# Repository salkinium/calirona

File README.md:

# Calirona: A calibration robot for Corona

The [Corona][corona] headphones use a HMC6343 compass for heading information which needs to be calibrated from time to time.
To do this, a robot rotates the headphones around two axis while the compass is in calibration mode.

The main design goals of this project are to:

-	calibrate the compass,
-	minimize the required technical knowledge to operate the robot,
-	test the compass functionality to catch the most obvious malfunctions.

This project was designed and manufactured at [The Media Computing Group][i10].

## Design

The robot can move the headphones around both two axes a full 360°, which are supported using ball bearings. The z-axis uses a dish which holds the headphones.

Since the power and signal lines for the headphones and second axis motor need to be relayed through both axis, the robot cannot rotate infinitely around its axis.  
Therefore two position switches exist, which allow the robot to rotate its axes into known safe positions before attempting a rotation.  
The robot will then rotate 360° around the x-axis, then 360° around the z-axis, and then reverse all rotations until it has reached the starting state again.

The robot is controlled by two buttons Start and Stop, and can display its internal state through leds for power, busy, headphone error and mechanical error.  
The mapping is as follows:

- START: initialize and start the calibration.
- STOP: stop robot movement (short press), release motors and reset robot (long press)
- Busy (blue): blinks, when an operation is in progress, otherwise off
- Headphone (orange): blinks, when no headphone is connected, or it is unresponsive (perhaps broken), otherwise on
- Mechanical Error (red): blinks, when the robot detected an invalid mechanical state (broken or blocked motor), otherwise off

## Usage

The basic usage of the robots is as follows:

1. Plug in the power cord. The green power led should light up and the headphone error led should blink.
2. Place the headphone into the holder drum and plug in the headphone jack. The headphone error led should stop blinking and turn on fully, unless the headphone is broken.
3. Press START. The robot will initialize its axes.
4. Press START again. The robot will do two rotations while calibrating the headphones.
5. Once the robot stopped moving, unplug the now calibrated headphones and remove them.

If the robot detected an invalid state during any of the actions, it will stop moving and blink an error led.

**Press the STOP button anytime to stop the robot from moving!**  
Pressing the STOP button for a longer time resets the robot.

## Organization

This repository is organized as follows:

- 	The *hardware* folder contains all hardware files for the robot.
	-	*hardware/et* contains the PCB schematics and layouts.
	-	*hardware/mech* contains the vector files of all mechanical parts of the robot (for the lasercutter).
- 	The *software* folder contains the software for the robot.
	- 	*software/source* contains the actual application code for this robot.
	-	*software/xpcc* contains the git submodule for the xpcc.io microcontroller framework.

All hardware and embedded software was designed by [Niklas Hauser][hauser].

[i10]: http://hci.rwth-aachen.de
[corona]: http://hci.rwth-aachen.de/corona
[hauser]: http://hci.rwth-aachen.de/hauser

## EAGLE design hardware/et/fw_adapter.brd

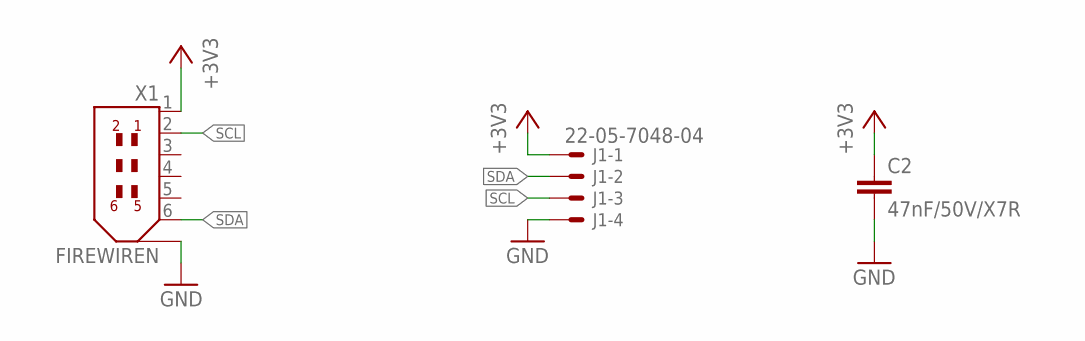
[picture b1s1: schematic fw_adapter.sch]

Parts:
C2: 47nF/50V/X7R; C0603K
J1: 22-05-7048-04; 7395-04
X1: FIREWIREN; IEEE1394_90DEG_PINS_NORMAL

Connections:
+3V3: C2.1, J1.1, X1.1
GND: C2.2, J1.4, X1.M1 (7), X1.M2 (7)
SCL: J1.3, X1.2
SDA: J1.2, X1.6

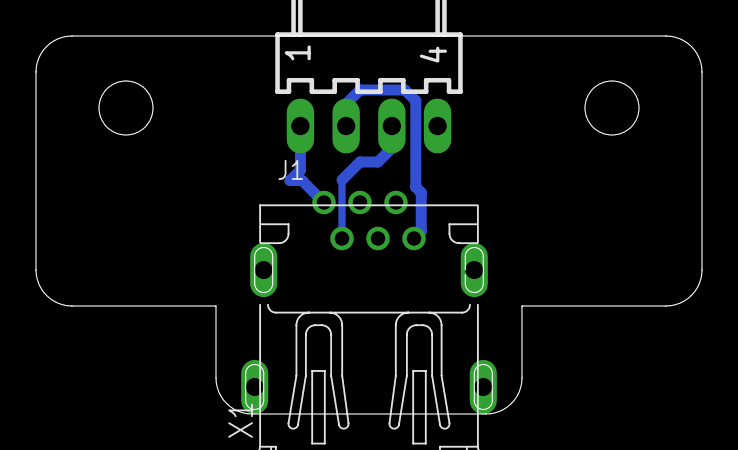
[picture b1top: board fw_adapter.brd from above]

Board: 2 copper layers, 37.0 x 21.0 mm, 3 parts (1 on the bottom side), 4 nets.

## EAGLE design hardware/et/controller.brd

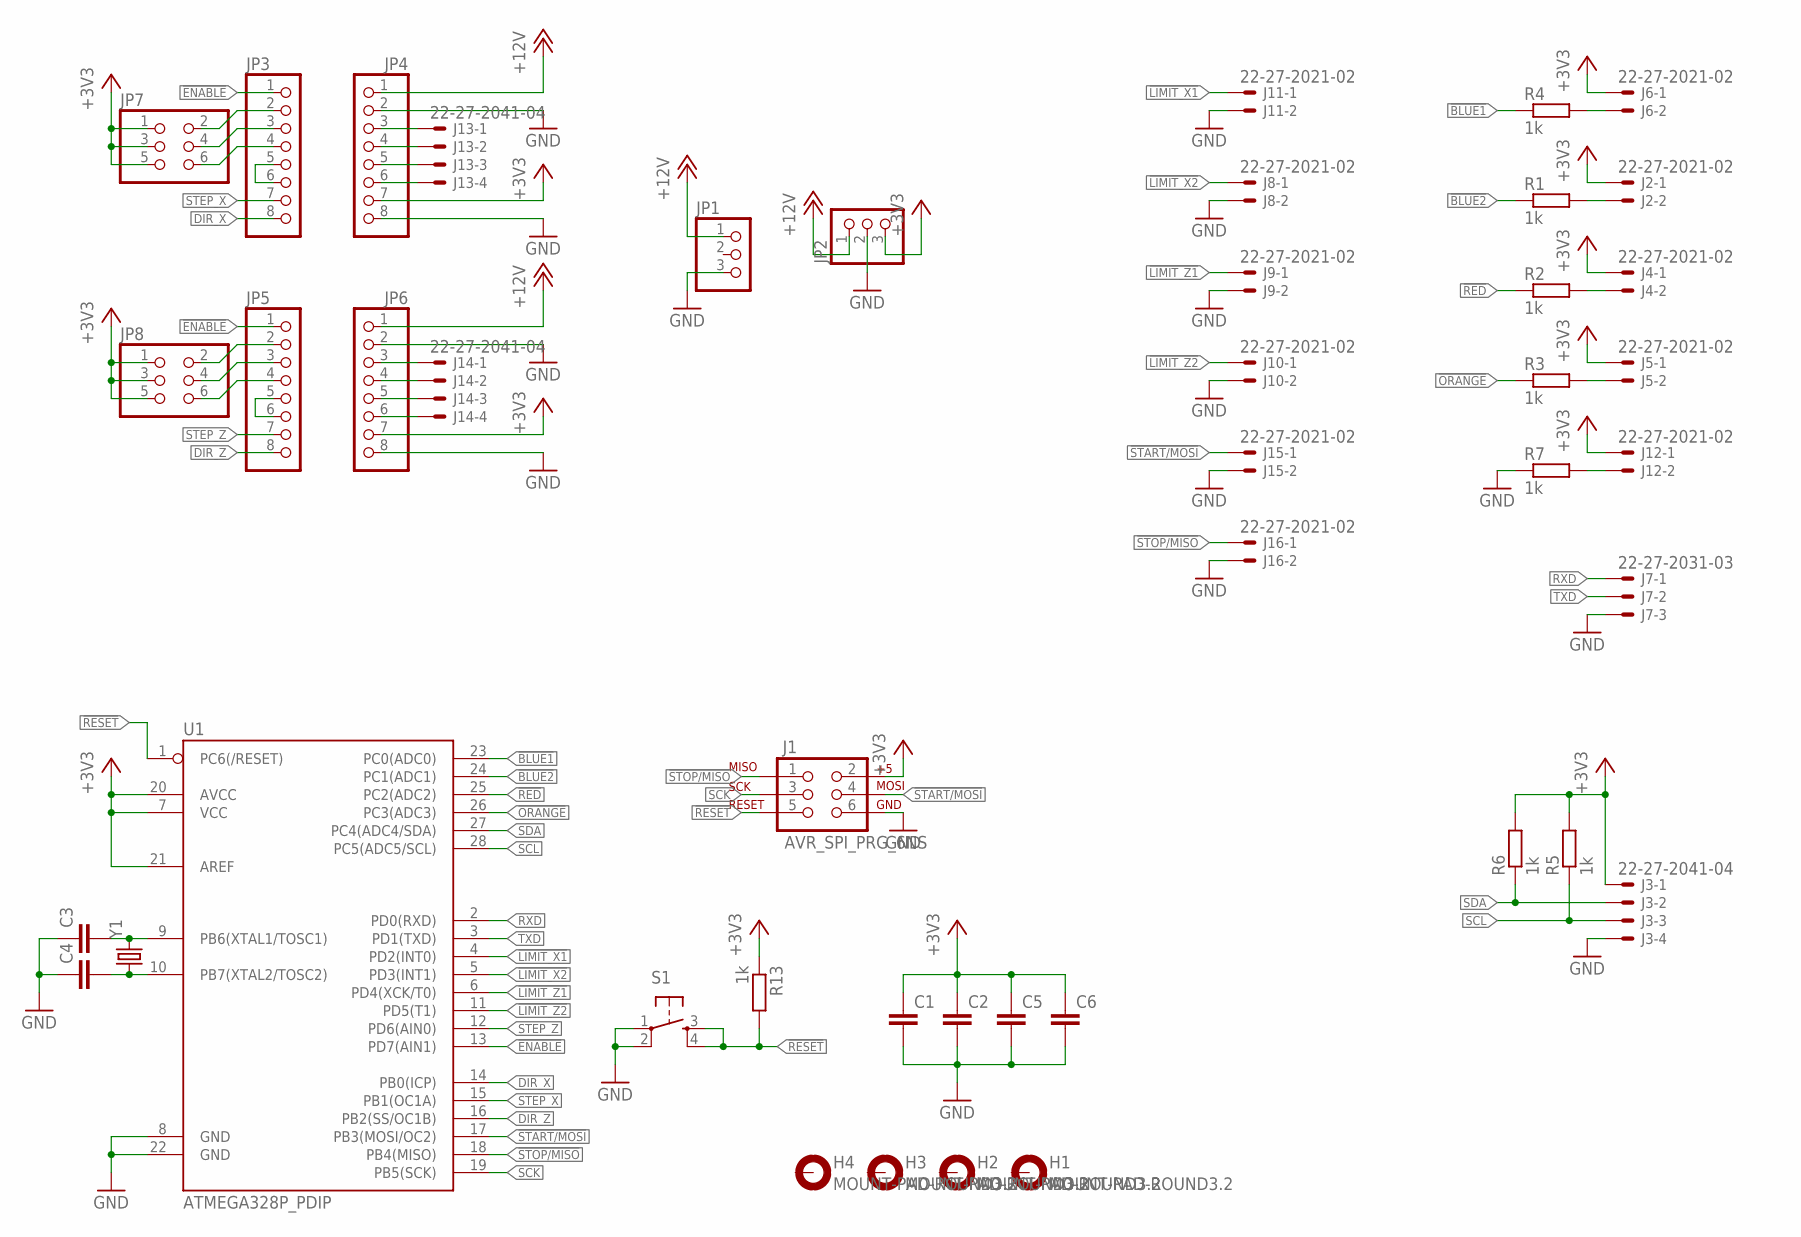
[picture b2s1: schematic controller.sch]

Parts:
C1, C2, C5, C6: C-EUC0603; C0603
C3, C4: C-EUC0603K; C0603K
H1, H2, H3, H4: MOUNT-PAD-ROUND3.2; 3,2-PAD
J1: AVR_SPI_PRG_6NS; 2X3-NS
J2, J4, J5, J6, J8, J9, J10, J11, J12, J15, J16: 22-27-2021-02; 6410-02
J3, J13, J14: 22-27-2041-04; 6410-04
J7: 22-27-2031-03; 6410-03
JP1, JP2: PINHD-1X3; 1X03
JP3, JP4, JP5, JP6: PINHD-1X8; 1X08
JP7, JP8: PINHD-2X3; 2X03
R1, R2, R3, R4, R5, R6, R7, R13: 1k; R0603
S1: TAC_SWITCHPTH; TACTILE-PTH
U1: ATMEGA328P_PDIP; DIL28-3
Y1: CRYSTALHC49UV; HC49U-V

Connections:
!BLUE1: R4.1, U1.23 (PC0(ADC0))
!BLUE2: R1.1, U1.24 (PC1(ADC1))
!ENABLE: JP3.1, JP5.1, U1.13 (PD7(AIN1))
!LIMIT_X1: J11.1, U1.4 (PD2(INT0))
!LIMIT_X2: J8.1, U1.5 (PD3(INT1))
!LIMIT_Z1: J9.1, U1.6 (PD4(XCK/T0))
!LIMIT_Z2: J10.1, U1.11 (PD5(T1))
!ORANGE: R3.1, U1.26 (PC3(ADC3))
!RED: R2.1, U1.25 (PC2(ADC2))
!RESET: J1.5, R13.2, S1.3, S1.4, U1.1 (PC6(/RESET))
!START/MOSI: J1.4, J15.1, U1.17 (PB3(MOSI/OC2))
!STOP/MISO: J1.1, J16.1, U1.18 (PB4(MISO))
+3V3: C1.1, C2.1, C5.1, C6.1, J1.2, J2.1, J3.1, J4.1, J5.1, J6.1, J12.1, JP2.3, JP4.7, JP6.7, JP7.1, JP7.3, JP7.5, JP8.1, JP8.3, JP8.5, R5.2, R6.2, R13.1, U1.7 (VCC), U1.20 (AVCC), U1.21 (AREF)
+12V: JP1.1, JP2.1, JP4.1, JP6.1
DIR_X: JP3.8, U1.14 (PB0(ICP))
DIR_Z: JP5.8, U1.16 (PB2(SS/OC1B))
GND: C1.2, C2.2, C3.1, C4.1, C5.2, C6.2, J1.6, J3.4, J7.3, J8.2, J9.2, J10.2, J11.2, J15.2, J16.2, JP1.3, JP2.2, JP4.2, JP4.8, JP6.2, JP6.8, R7.1, S1.1, S1.2, U1.8 (GND), U1.22 (GND)
unnamed: C3.2, U1.9 (PB6(XTAL1/TOSC1)), Y1.2
unnamed: C4.2, U1.10 (PB7(XTAL2/TOSC2)), Y1.1
unnamed: J4.2, R2.2
unnamed: J2.2, R1.2
unnamed: J5.2, R3.2
unnamed: J6.2, R4.2
unnamed: JP3.5, JP3.6
unnamed: JP3.4, JP7.6
unnamed: JP3.3, JP7.4
unnamed: JP3.2, JP7.2
unnamed: J12.2, R7.2
unnamed: JP5.5, JP5.6
unnamed: JP5.4, JP8.6
unnamed: JP5.3, JP8.4
unnamed: JP5.2, JP8.2
unnamed: J13.1, JP4.3
unnamed: J13.2, JP4.4
unnamed: J13.3, JP4.5
unnamed: J13.4, JP4.6
unnamed: J14.1, JP6.3
unnamed: J14.2, JP6.4
unnamed: J14.3, JP6.5
unnamed: J14.4, JP6.6
RXD: J7.1, U1.2 (PD0(RXD))
SCK: J1.3, U1.19 (PB5(SCK))
SCL: J3.3, R5.1, U1.28 (PC5(ADC5/SCL))
SDA: J3.2, R6.1, U1.27 (PC4(ADC4/SDA))
STEP_X: JP3.7, U1.15 (PB1(OC1A))
STEP_Z: JP5.7, U1.12 (PD6(AIN0))
TXD: J7.2, U1.3 (PD1(TXD))

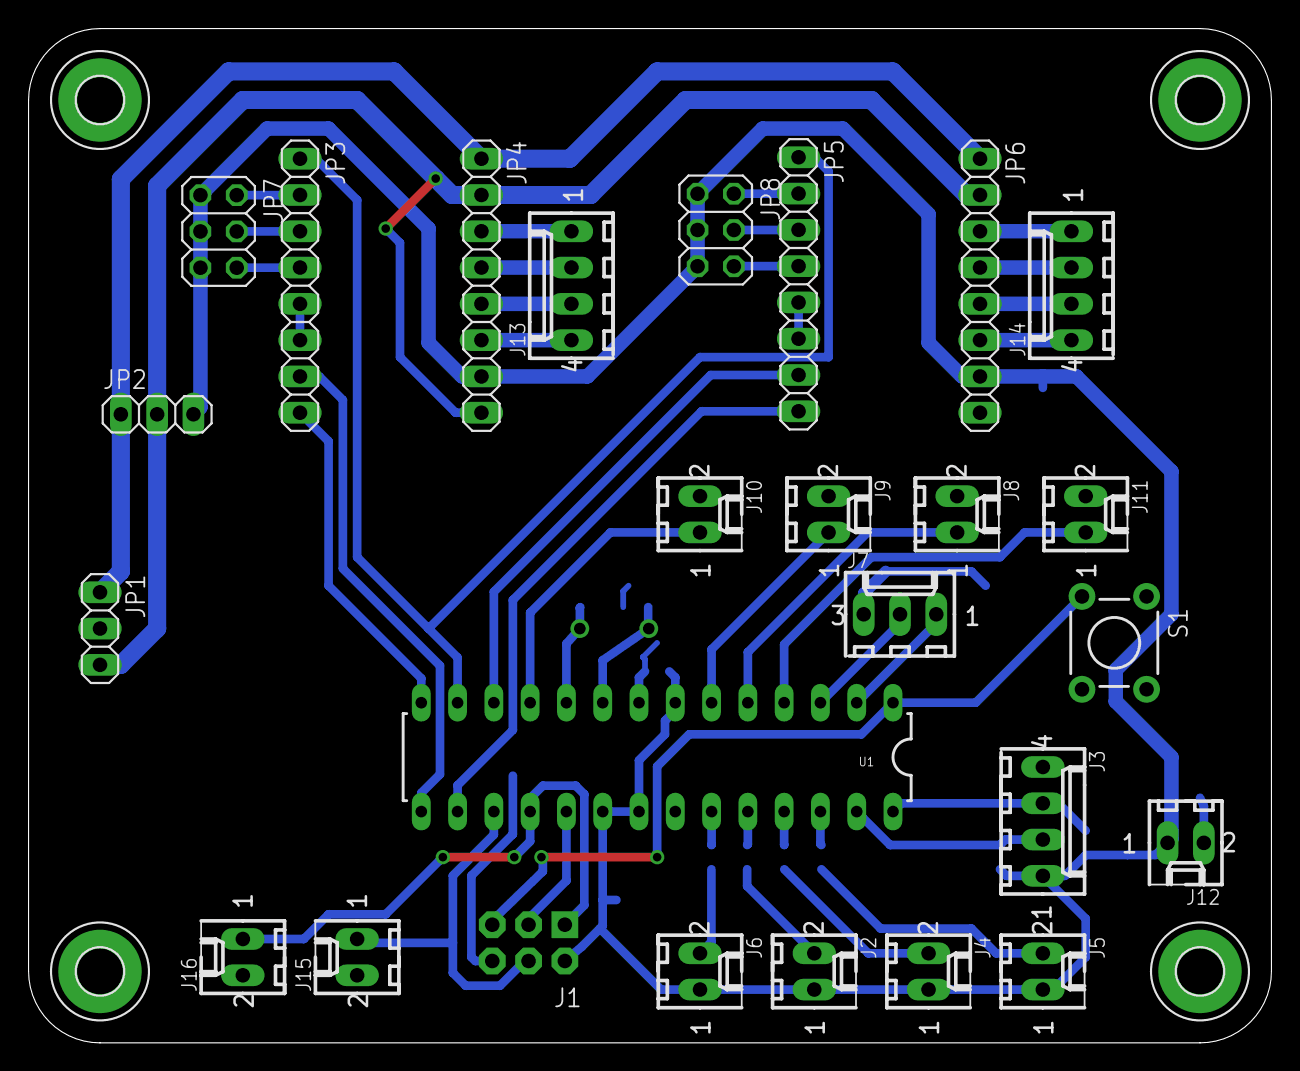
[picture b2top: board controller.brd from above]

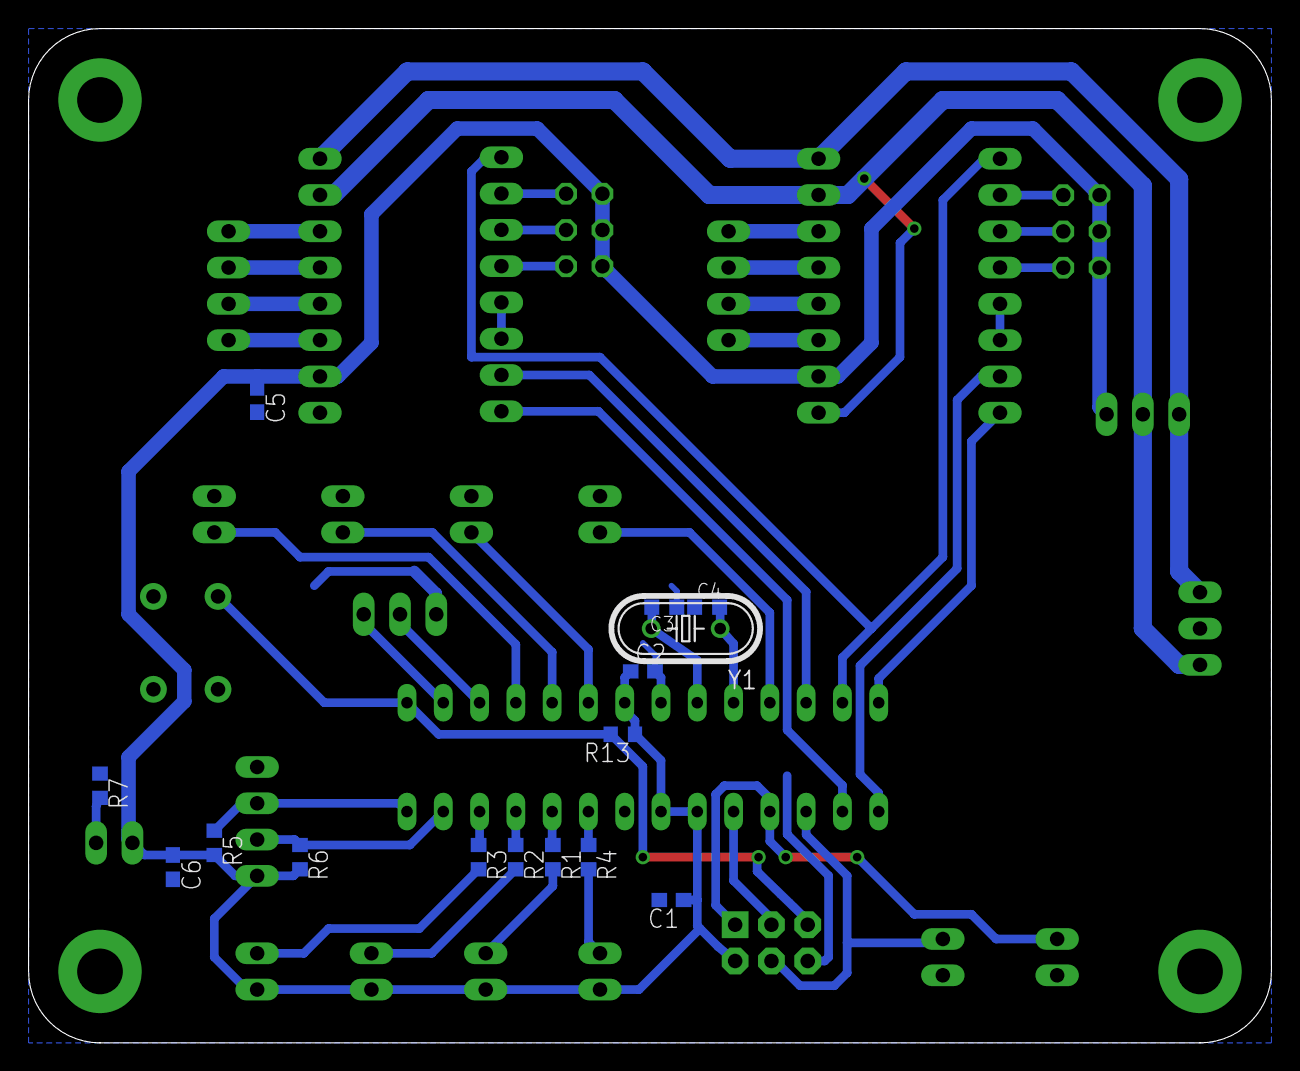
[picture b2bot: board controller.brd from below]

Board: 2 copper layers, 87.0 x 71.0 mm, 45 parts (15 on the bottom side), 47 nets.

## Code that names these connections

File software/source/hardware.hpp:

// coding: utf-8
/* Copyright (c) 2014, Niklas Hauser
* All Rights Reserved.
*/
// ----------------------------------------------------------------------------

#ifndef CALIRONA_HARDWARE
#define CALIRONA_HARDWARE

#include <xpcc/architecture/platform.hpp>

using namespace xpcc::atmega;

// IO #########################################################################
// ATMEL ATMEGA328P
//                     +-v-+
//      (!RESET) PC6  1|   |28  PC5 (SCL)
//         (RXD) PD0  2|   |27  PC4 (SDA)
//         (TXD) PD1  3|   |26  PC3 (!HEADPHONE)
//   (!X_LIMIT1) PD2  4|   |25  PC2 (!MECH_ERROR)
//   (!X_LIMIT2) PD3  5|   |24  PC1 (!BUSY2)
//   (!Z_LIMIT1) PD4  6|   |23  PC0 (!BUSY1)
//               VCC  7|   |22  GND
//               GND  8|   |21  AREF
//       (XTAL1) PB6  9|   |20  AVCC
//       (XTAL2) PB7 10|   |19  PB5 (SCK)
//   (!Z_LIMIT2) PD5 11|   |18  PB4 (!START/MISO)
// (Z_STEP/OC0A) PD6 12|   |17  PB3 (!STOP/MOSI)
//     (!ENABLE) PD7 13|   |16  PB2 (Z_DIR)
//       (X_DIR) PB0 14|   |15  PB1 (X_STEP/OC1A)
//                     +---+

typedef xpcc::avr::SystemClock systemClock;

// motor step counters
uint16_t t0_steps;
uint16_t t1_steps;

// Motors
typedef xpcc::GpioInverted< GpioOpenDrain< GpioD7 > > XZ_Enable;

// X-Axis
typedef xpcc::GpioInverted< GpioInputD2 > X_Limit1;
typedef xpcc::GpioInverted< GpioInputD3 > X_Limit2;
typedef GpioOutputB0 X_Dir;
typedef GpioOutputB1 X_Step;

// Z-Axis
typedef xpcc::GpioInverted< GpioInputD4 > Z_Limit1;
typedef xpcc::GpioInverted< GpioInputD5 > Z_Limit2;
typedef GpioOutputB2 Z_Dir;
typedef GpioOutputD6 Z_Step;

// LEDs
typedef xpcc::GpioInverted< GpioOutputC0 > LED_Busy1;
typedef xpcc::GpioInverted< GpioOutputC1 > LED_Busy2;
typedef xpcc::GpioInverted< GpioOutputC2 > LED_Headphone;
typedef xpcc::GpioInverted< GpioOutputC3 > LED_MechError;

// Buttons
typedef xpcc::GpioInverted< GpioInputB4 > ButtonStart;
typedef xpcc::GpioInverted< GpioInputB3 > ButtonStop;

// COMMUNICATION ##############################################################
typedef GpioC4 Sda;
typedef GpioC5 Scl;
typedef I2cMaster Twi;

// SERIAL DEBUG ###############################################################
#include <xpcc/io/iodevice_wrapper.hpp>
typedef Uart0 Uart;
xpcc::IODeviceWrapper< Uart, xpcc::IOBuffer::BlockIfFull > outputDevice;

#include <xpcc/debug/logger/style_wrapper.hpp>
#include <xpcc/debug/logger/style/prefix.hpp>
#include <xpcc/debug/logger.hpp>
xpcc::log::StyleWrapper< xpcc::log::Prefix< char[10] > > loggerDeviceDebug (
		xpcc::log::Prefix< char[10] > ("Debug:   ", outputDevice ) );
xpcc::log::Logger xpcc::log::debug( loggerDeviceDebug );

xpcc::log::StyleWrapper< xpcc::log::Prefix< char[10] > > loggerDeviceInfo (
		xpcc::log::Prefix< char[10] > ("Info:    ", outputDevice ) );
xpcc::log::Logger xpcc::log::info( loggerDeviceInfo );

xpcc::log::StyleWrapper< xpcc::log::Prefix< char[10] > > loggerDeviceWarning (
		xpcc::log::Prefix< char[10] > ("Warning: ", outputDevice ) );
xpcc::log::Logger xpcc::log::warning( loggerDeviceWarning );

xpcc::log::StyleWrapper< xpcc::log::Prefix< char[10] > > loggerDeviceError (
		xpcc::log::Prefix< char[10] > ("Error:   ", outputDevice ) );
xpcc::log::Logger xpcc::log::error( loggerDeviceError );

#undef	XPCC_LOG_LEVEL
#define	XPCC_LOG_LEVEL xpcc::log::DEBUG

// TASKS ######################################################################
#include "tasks/task_buttons.hpp"
task::Buttons buttons;
#include "tasks/task_leds.hpp"
task::Leds leds;

#include "tasks/task_headphone.hpp"
task::Headphone headphone(leds);

#include "tasks/task_mechanics.hpp"
task::Mechanics mechanics(leds, buttons);

#include "tasks/task_manager.hpp"
task::Manager manager(buttons, leds, headphone, mechanics);

#endif // CALIRONA_HARDWARE

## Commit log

2013-08-24 Initial commit.
2013-08-24 Add Readme and License.
2013-08-29 Add A4988 stepper motor driver. Update xpcc.
2013-08-30 Add Rotate Task without I2c control yet. Move hardware definitions into own file.
2013-08-30 Fix timer init, xpcc::Clock was running twice as fast.
2013-09-22 Add manager task. Add debounced start and stop buttons. Update xpcc.io.
2013-09-22 Update Readme.
2013-09-24 Software: Add Logger output. Fix I2c problems.
2013-09-24 Software: Update xpcc.io.
2013-10-01 Software: Move Dir and Step pins of Z axis. Add code to stop Motors, when stop button is pressed. Update xpcc.io.
2014-09-24 Update software.
2014-10-21 Increase uart buffer through xpcc parameter magic.
2014-10-21 Fix motor problems with time tracking by simply counting the steps.
2014-10-21 Add timeout to Mechanics class to release the motors after 30s.
2014-10-21 Manager class now handles the basic calibration and rotation tasks.
2014-10-21 Decrease verbosity a little.
2014-10-21 Update xpcc submodule.
2014-10-22 Make mechanics a little faster.
2014-10-22 Add proper enter- and exitUserCalibrationMode code with offset readout.
2014-10-22 Update manager application code incl. failures.
2014-10-22 Add PCB schematics and layouts.
2014-10-22 Add all hardware files for the robot’s structure.
2014-10-22 Set IIR Filter to 5.
2014-10-22 Invert Headphone Led behaviour.
2014-10-22 Reduce calibration timeout, to limit mechanical damage by overdrawn limit switch.
2014-10-22 Fix xpcc toolpath for project.
2014-10-22 Move remaining button code from main loop to manager task.
2014-10-22 Refactor to use logical instead of physical Gpio states.
2014-10-22 Beautify code.
2014-10-24 Beautify.
2014-10-26 Remove unused task rotate.
2014-10-26 Update for changes in xpcc submodule.
2014-10-27 Make Calibrate task a little safer.
2014-11-03 Adapt for a change in x-axis end switch position.
2014-11-04 Fix calirona user guide. Fix Readme.
2014-11-04 Fix reset of mech error leds before it was triggered.
2015-01-30 Update xpcc submodule and adapt for changes.

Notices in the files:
parts and their libraries:
SparkFun-DigitalIC: Licensing: CC v3.0 Share-Alike You are welcome to use this library for commercial purposes.
